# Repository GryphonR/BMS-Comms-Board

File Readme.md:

# eChook BMS Comunications Master Board
This project is heavily inspired by the [SimpBMS](https://github.com/Tom-evnut/SimpBMS) project by [Tom-evnut](https://github.com/Tom-evnut). The SimpBMS Hardware was never open-sourced, and has become obsolete post-COVID with the demise of the Teensy 3.x development boards.  
This board uses a Teensy 4.1 to mirror, then expand on the functionality of the original SimpBMS board.

While effort has been made to maintain some cross compatibility with the SimpBMS in connector choices and pinouts, this board is **not** a drop in replacement.

## License
This hardware design is released under a non-commercial open hardware licence, is provided **"as is"**, without warranty of any kind, express or implied. See the License.md file for details.

## Features

**ALL UNTESTED**

In addition to an expanded feature set over the SimpBMS, this board offers far more comprehensive circuit protection, most notably offering electrically isolated power and comms for the Battery Module connections, short circuit protection on all off board voltage feeds, so a harness issue does not take down the BMS, and 24v overvoltage protection on all digital and analogue inputs.

IO Overview:  
- 3 CAN Busses (All ESD protected, one Isolated for Battery Module comms).
    - Switchable Terminating Resistor for each bus.
- 2 UART, ESD protected and buffered.
    - One Isolated for Tesla Battery Module Comms.
    - One non-isolated, with selectable voltage levels.
- 1 RS-458/Modbus Interface
- 4 24v safe digital inputs
- 4 Monitored and Overcurrent protected 12v 5A High Side Drivers
- 4 5A Low Side Drivers
- 3 Short Circuit protected 12v outputs
- 4 Short Circuit Protected 5V outputs (One Isolated)
- 2 Analogue Inputs for Current Sensor signals, 24V safe.
- 1 I2C header for 0.91" OLED display.
- 1 SD card slot on the Teensy 4.1 to allow for logging with RTC timestamping.
- Ultra Bright Red error LED
- Warning Buzzer indicating BMS error or blown fuse (On, unless actively turned off by Teensy)

A little more detail:  
- Networks:
    - Electronically isolated communication busses for battery slave module communications.
        - Isolated 5V UART port for Tesla Module Communications (Teensy Serial2)
        - Isolated 600mA 5V supply 
        - Isolated CAN (Teensy CAN1) Connection for (most other) battery modules that communicate over CAN
    - Two non-isolated CAN busses, one exposed on the RJ-45 connector (CAN3), a second exposed on the J5 Auxillary Comms connector (CAN2)
    - One RS-485/MODBUS interface (Teensy Serial8)
    - RJ-45 connector with VICTRON compatible pin out as default, but 'Pick Your Own Pinout' pads on the bottom of the board to allow this to be modified to any application with a bit of soldering.
    - Serial output on J5 (Serial7). Voltage is selectable between 5V and 3.3v by solder jumper on rear of board.
- I/O
    - 4 High Impedence digital inputs, up to 24V.
    - 4 12V High Side Driver outputs, each with voltage, current and temperature monitoring, automatic over temperature, short circuit protection and error state reporting.
    - 4 PWM Capable Low Side Driver outputs with over current/short circuit protection, over temperature protecton. LOW Speed PWM only - testing needed, suspect <2KHz.
- Voltage Supply
    - 5V 500mA Isolated voltage supply for Tesla BMS Boards. Short circuit protected with red fault LED
    - 3 5V 500mA Voltage supplies on J2, J4 and J5, each short circuit protected with red fault LED
    - 3 12v Supplies on J4, Pins 10 and 11 sharing one short circuit protection ciruit, Pin 9 with it's own short circuit protection circuit.
- Warning System
    - Audible warning via a buzzer. This sounds if the onboard fuse blows, or if it is not actively being turned off by the Teensy.
    - Visual warning via 10mA Red LED. This is driven by the Teensy.
    - Heartbeat - Green LED located in cheesy silkscreen image of a heart will blink regularly if the system is healthy.

## Firmware
Due to the swap to a Teensy 4.1, expanded capabilities of the board, and a few pinout changes that go along with both of those, this board is not directly compatible with the SimpBMS code. There is an updated fork of the TeslaBMSV2 firmware adapted for this board here **TODO - link**.

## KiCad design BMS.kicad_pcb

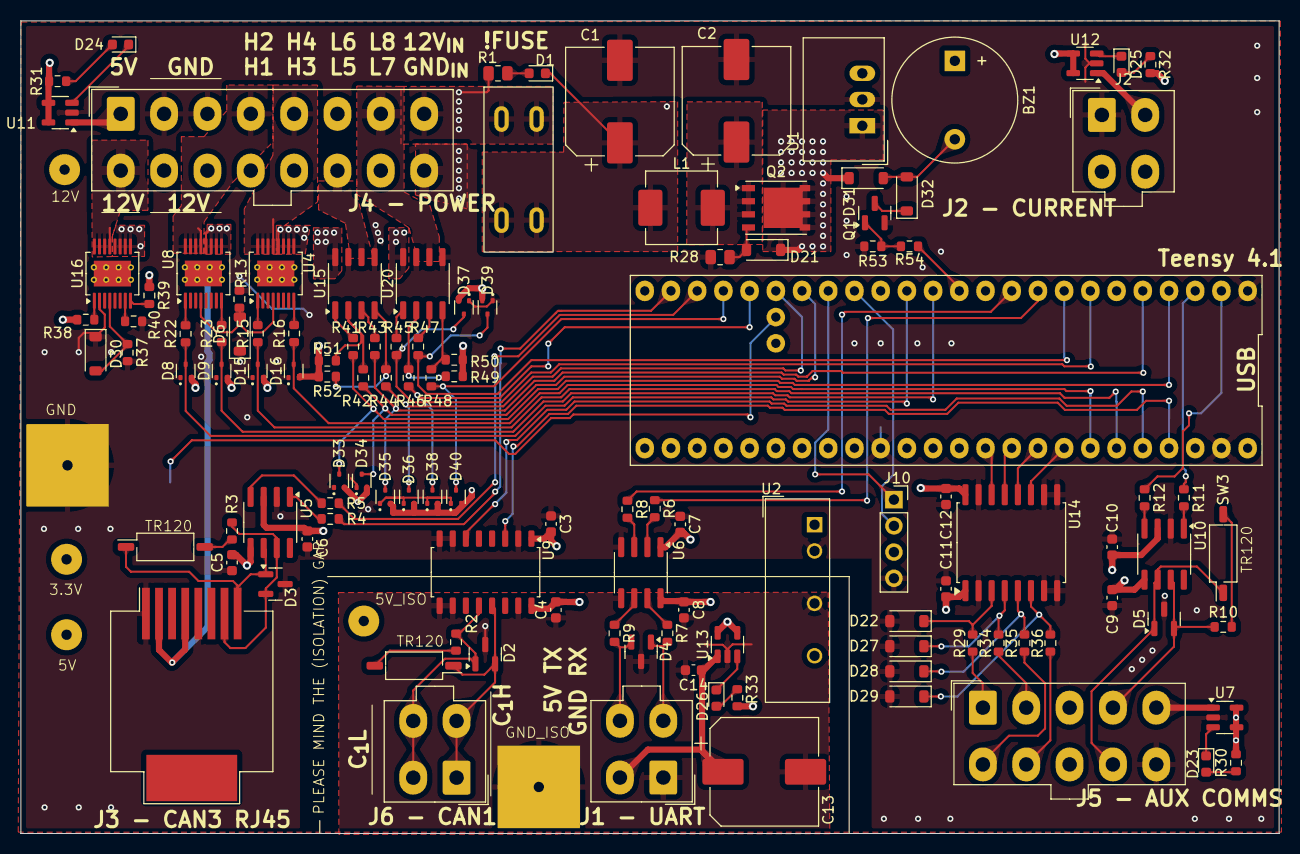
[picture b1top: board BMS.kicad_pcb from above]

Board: 4 copper layers, 121.9 x 78.7 mm, 127 parts (1 on the bottom side), 108 nets.

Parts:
BT1: Battery_Cell; BatteryHolder_Keystone_1060_1x2032
BZ1: Buzzer; Buzzer_12x9.5RM7.6
C1, C2, C13: 470uF; CP_Elec_10x10
C3, C4, C5, C6, C7, C8, C9, C10, C11, C12, C14: 1uF; C_0603_1608Metric
D1: LED; LED_0603_1608Metric
D2, D3, D4, D5: PESD1CAN; SOT-23
D6, D30, D31, D32: D; D_SOD-123
D8, D9, D15, D16, D33, D34, D35, D36, D37, D38, D39, D40: BAT54S; SOT-523
D21: 10V; D_SOD-123
D22, D27, D28, D29: 4.7V Zener 500mW; D_SOD-123
D23, D24, D25, D26: LED_RED; LED_0603_1608Metric
F1: Mini Blade Fuse (10A); XFCN XF-508P-B-B
J1, J2, J6: Conn_02x02_Counter_Clockwise; Molex_Mini-Fit_Jr_5566-04A_2x02_P4.20mm_Vertical
J3: RJ45; RJ45_Molex_0855135013_Vertical
J4: Conn_02x08_Top_Bottom; Molex_Mini-Fit_Jr_5566-16A_2x08_P4.20mm_Vertical
J5: Conn_02x05_Top_Bottom; Molex_Mini-Fit_Jr_5566-10A_2x05_P4.20mm_Vertical
J10: OLED; PinSocket_1x04_P2.54mm_Vertical
L1: 1.5uH; L_Changjiang_FXL0618
Q1: BSS138LT1G; SOT-23
Q2: HSBA100P03; PowerPAK_SO-8_Single
R1, R28: 10k; R_0805_2012Metric
R2, R3, R10: 120; R_0603_1608Metric
R4, R5, R6, R7, R8, R9, R11, R12: 330R; R_0603_1608Metric
R13, R29, R34, R35, R36, R37, R53: 4.7k; R_0603_1608Metric
R15, R16, R22, R23, R38, R39: 15k; R_0603_1608Metric
R30, R31, R32, R33: 3.3k; R_0603_1608Metric
R40, R41, R42, R43, R44, R45, R46, R47, R48: 1k; R_0603_1608Metric
R49, R50, R51, R52: 47k; R_0603_1608Metric
R54: 330; R_0603_1608Metric
SW1, SW2, SW3: SW_DIP_x01; SW_DIP_SPSTx01_Slide_Copal_CHS-01B_W7.62mm_P1.27mm
TP1, TP4: TestPoint; Clip_TP
TP2, TP3, TP5, TP6: TestPoint; STD_TP
U1: K7805M-1000R3; Converter_DCDC_TRACO_TSR-1_THT
U2: B0505S-3WR2; Converter_DCDC_TRACO_TBA1-xxxxE_Single_THT
U3: Teensy4.1; Teensy_4.1_RTC
U4, U8, U16: VND7050AJTR; PowerSSO-16-1EP_3.9x4.9mm_P0.5mm_EP2.5x3.61mm_ThermalVias
U5, U10: TJA1051T/3/1J; SOIC-8_3.9x4.9mm_P1.27mm
U6: ISO7331C; SOIC-8_3.9x4.9mm_P1.27mm
U7, U11, U12, U13: TPS2051CDBV; SOT-23-5
U9: ISO1050DWR; SOP-16_4.55x10.3mm_P1.27mm
U14: CA-IS3740; SOIC-16W_7.5x10.3mm_P1.27mm
U15, U20: VNLD5090TR-E; SO-8_3.9x4.9mm_P1.27mm

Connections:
+3.3V: C3.2, C5.2, C7.2, C9.2, C12.2, D8.2 (K), D9.2 (K), D15.2 (K), D16.2 (K), D33.2 (K), D34.2 (K), D35.2 (K), D36.2 (K), D37.2 (K), D38.2 (K), D39.2 (K), D40.2 (K), J10.3, R49.2, R50.2, R51.2, R52.2, TP6.1, U3.15 (3V3), U3.46 (3V3), U3.50 (3.3V), U5.5 (Vref), U6.1 (VCC1), U9.1 (VCC1), U10.5 (Vref), U14.16 (VDD_{B})
+5V: C6.2, C10.2, C11.1, R30.2, R31.2, R32.2, R38.1, R39.1, TP5.1, U1.3 (Vout), U2.1 (+Vin), U3.48 (VIN), U5.3 (VDD), U7.4 (EN), U7.5 (IN), U10.3 (VDD), U11.4 (EN), U11.5 (IN), U12.4 (EN), U12.5 (IN), U14.1 (VDD_{A})
+5V_ISO: C4.2, C8.2, R33.2, TP3.1, U2.6 (+Vout), U6.8 (VCC2), U9.16 (VCC2), U13.4 (EN), U13.5 (IN)
+12V: D21.1 (K), D31.1 (K), J3.2, J3.4, Q2.5 (D), TP2.1, U1.1 (Vin), U4.17 (V_{cc}), U8.17 (V_{cc}), U16.17 (V_{cc})
/12V_INPUT: BZ1.1 (+), F1.1, J4.8, R1.2
/12V_Out_Bank1: J4.9, U16.13 (Output_0), U16.14 (Output_0), U16.15 (Output_0), U16.16 (Output_0)
/12V_Out_Bank2: J4.10, J4.11, U16.9 (Output_1), U16.10 (Output_1), U16.11 (Output_1), U16.12 (Output_1)
/12V_Output_Protection/Driver_Gnd: D30.2 (A), R37.1, U16.4 (GND)
/Buzzer_-ve: D32.1 (K), Q1.3 (D)
/Buzzer_Logic: R54.2, U3.12 (10_CS_MQSR)
/CAN1_HIGH_ISO: D2.2 (A2), J6.1, J6.3, SW1.1, U9.13 (CANH)
/CAN1_LOW_ISO: D2.1 (A1), J6.2, J6.4, R2.1, U9.12 (CANL)
/CAN1_RX: U3.45 (23_A9_CRX1_MCLK1), U9.3 (RXD)
/CAN1_TX: U3.44 (22_A8_CTX1), U9.6 (TXD)
/CAN2_HIGH: D5.2 (A2), J5.4, R10.1, U10.7 (CANH)
/CAN2_LOW: D5.1 (A1), J5.9, SW3.1, U10.6 (CANL)
/CAN2_RX: R12.1, U3.2 (0_RX1_CRX2_CS1)
/CAN2_TX: R11.1, U3.3 (1_TX1_CTX2_MISO1)
/CAN3_HIGH: D3.2 (A2), J3.7, R3.1, U5.7 (CANH)
/CAN3_LOW: D3.1 (A1), J3.8, SW2.1, U5.6 (CANL)
/CAN3_RX: R5.1, U3.22 (30_CRX3)
/CAN3_TX: R4.1, U3.23 (31_CTX3)
/High Side Drivers/Driver_Gnd: D6.2 (A), R13.1, U4.4 (GND), U8.4 (GND)
/In_1: J5.1, R29.1
/In_2: J5.2, R34.1
/In_3: J5.6, R35.1
/In_4: J5.7, R36.1
/Logic_IN_1: U3.38 (16_A2_RX4_SCL1), U14.14 (Out_{1})
/Logic_IN_2: U3.39 (17_A3_TX4_SDA1), U14.13 (Out_{2})
/Logic_IN_3: U3.40 (18_A4_SDA), U14.12 (Out_{3})
/Logic_IN_4: U3.41 (19_A5_SCL), U14.11 (Out_{4})
/OUT1_HSD_LOGIC: D9.3 (COM), R23.1, U3.13 (11_MOSI_CTX1)
/OUT1_HSD_PWR: J4.12, U8.9 (Output_1), U8.10 (Output_1), U8.11 (Output_1), U8.12 (Output_1)
/OUT2_HSD_LOGIC: D8.3 (COM), R22.1, U3.14 (12_MISO_MQSL)
/OUT2_HSD_PWR: J4.4, U8.13 (Output_0), U8.14 (Output_0), U8.15 (Output_0), U8.16 (Output_0)
/OUT3_HSD_LOGIC: D16.3 (COM), R16.1, U3.42 (20_A6_TX5_LRCLK1)
/OUT3_HSD_PWR: J4.13, U4.9 (Output_1), U4.10 (Output_1), U4.11 (Output_1), U4.12 (Output_1)
/OUT4_HSD_LOGIC: D15.3 (COM), R15.1, U3.43 (21_A7_RX5_BCLK1)
/OUT4_HSD_PWR: J4.5, U4.13 (Output_0), U4.14 (Output_0), U4.15 (Output_0), U4.16 (Output_0)
/OUT5_LSD_LOGIC: D33.3 (COM), R41.1, U3.4 (2_OUT2)
/OUT5_LSD_PWR: J4.14, U15.6 (Drain_{2})
/OUT5_LSD_Status: D34.3 (COM), R42.1, U3.18 (26_A12_MOSI1)
/OUT6_LSD_LOGIC: D35.3 (COM), R43.1, U3.5 (3_LRCLK2)
/OUT6_LSD_PWR: J4.6, U15.8 (Drain_{1})
/OUT6_LSD_Status: D36.3 (COM), R44.1, U3.19 (27_A13_SCK1)
/OUT7_LSD_LOGIC: D37.3 (COM), R45.1, U3.7 (5_IN2)
/OUT7_LSD_PWR: J4.7, U20.6 (Drain_{2})
/OUT7_LSD_Status: D38.3 (COM), R46.1, U3.20 (28_RX7)
/OUT8_LSD_LOGIC: D39.3 (COM), R47.1, U3.8 (6_OUT1D)
/OUT8_LSD_PWR: J4.15, U20.8 (Drain_{1})
/OUT8_LSD_Status: D40.3 (COM), R48.1, U3.21 (29_TX7)
/Overcurrent_Protection1/V_{OUT}: J4.1, U11.1 (OUT)
/Overcurrent_Protection2/V_{OUT}: J2.2, U12.1 (OUT)
/Overcurrent_Protection3/V_{OUT}: C13.1, C14.1, J1.2, U13.1 (OUT)
/Overcurrent_Protection/V_{OUT}: J5.5, U7.1 (OUT)
/RTC_BATT_+: BT1.1 (+), U3.49 (V_BATT_RTC)
/SERIAL_RX: R6.1, U3.9 (7_RX2_OUT1A)
/SERIAL_TX: R8.1, U3.10 (8_TX2_IN1)
/UART_RX_ISO: D4.1 (A1), J1.3, R7.2
/UART_TX_ISO: D4.2 (A2), J1.4, R9.2
GND: BT1.2 (-), C1.2, C2.2, C3.1, C5.1, C6.1, C7.1, C9.1, C10.1, C11.2, C12.1, D3.3 (common), D5.3 (common), D6.1 (K), D8.1 (A), D9.1 (A), D15.1 (A), D16.1 (A), D22.2 (A), D27.2 (A), D28.2 (A), D29.2 (A), D30.1 (K), D33.1 (A), D34.1 (A), D35.1 (A), D36.1 (A), D37.1 (A), D38.1 (A), D39.1 (A), D40.1 (A), J2.1, J3.1, J3.5, J4.2, J4.3, J4.16, J5.10, J10.4, Q1.2 (S), R13.2, R28.1, R37.2, R40.1, R53.2, TP4.1, U1.2 (GND), U2.2 (-Vin), U3.1 (GND), U3.34 (GND), U3.47 (GND), U5.2 (VSS), U6.4 (GND1), U7.2 (GND), U9.2 (GND1), U9.7 (GND1), U9.8 (GND1), U10.2 (VSS), U11.2 (GND), U12.2 (GND), U14.2 (GND_{A}), U14.7 (EN_{A}), U14.8 (GND_{A}), U14.9 (GND_{B}), U14.10 (EN_{B}), U14.15 (GND_{B}), U15.5 (Source_{2}), U15.7 (Source_{1}), U16.2 (~FaultRST), U20.5 (Source_{2}), U20.7 (Source_{1})
GND_ISO: C4.1, C8.1, C13.2, C14.2, D2.3 (common), D4.3 (common), J1.1, TP1.1, U2.4 (-Vout), U6.5 (GND2), U9.9 (GND2), U9.10 (GND2), U9.15 (GND2), U13.2 (GND)
I2C_SCL: J10.2, U3.16 (24_A10_TX6_SCL2)
I2C_SDA: J10.1, U3.17 (25_A11_RX6_SDA2)
unnamed: BZ1.2 (-), D31.2 (A), D32.2 (A)
unnamed: C2.1, L1.2, Q2.1 (S), Q2.2 (S), Q2.3 (S)
unnamed: D1.2 (A), R1.1
unnamed: C1.1, D1.1 (K), F1.2, L1.1
unnamed: D21.2 (A), Q2.4 (G), R28.2
unnamed: D22.1 (K), R29.2, U14.3 (In_{1})
unnamed: D23.2 (A), R30.1
unnamed: D23.1 (K), U7.3 (~FLT)
unnamed: D24.2 (A), R31.1
unnamed: D24.1 (K), U11.3 (~FLT)
unnamed: D25.2 (A), R32.1
unnamed: D25.1 (K), U12.3 (~FLT)
unnamed: D26.2 (A), R33.1
unnamed: D26.1 (K), U13.3 (~FLT)
unnamed: D27.1 (K), R34.2, U14.4 (In_{2})
unnamed: D28.1 (K), R35.2, U14.5 (In_{3})
unnamed: D29.1 (K), R36.2, U14.6 (In_{4})
unnamed: Q1.1 (G), R53.1, R54.1
unnamed: R2.2, SW1.2
unnamed: R3.2, SW2.2
unnamed: R10.2, SW3.2
unnamed: R15.2, U4.1 (Input_0)
unnamed: R16.2, U4.8 (Input_1)
unnamed: R5.2, U5.4 (RXD)
unnamed: R4.2, U5.1 (TXD)
unnamed: R7.1, U6.7 (INA)
unnamed: R8.2, U6.3 (INB)
unnamed: R6.2, U6.2 (OUTA)
unnamed: R9.1, U6.6 (OUTB)
unnamed: R22.2, U8.1 (Input_0)
unnamed: R23.2, U8.8 (Input_1)
unnamed: R12.2, U10.4 (RXD)
unnamed: R11.2, U10.1 (TXD)
unnamed: R41.2, U15.1 (IN_{1})
unnamed: R43.2, U15.3 (IN_{2})
unnamed: R42.2, R51.1, U15.2 (Status_{1})
unnamed: R44.2, R52.1, U15.4 (Status_{2})
unnamed: R38.2, U16.1 (Input_0)
unnamed: R39.2, U16.8 (Input_1)
unnamed: R40.2, U16.7 (Multisense)
unnamed: R45.2, U20.1 (IN_{1})
unnamed: R47.2, U20.3 (IN_{2})
unnamed: R46.2, R49.1, U20.2 (Status_{1})
unnamed: R48.2, R50.1, U20.4 (Status_{2})

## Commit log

2025-04-19 Added isolated CAN, UART and PWR
2025-05-06 Adding BOM Info
2025-05-06 Adding Part Numbers
2025-05-06 Updated Isolated CANTX
2025-05-07 Connectors, high side circuits added, layout progressed
2025-05-08 Added LSD, HSD, Improved Layout
2025-05-12 Added 12v Out Protection, generally completed layout
2025-05-13 All the diodes, and other layout work
2025-05-15 Layout, smaller resistors and HB + Error LEDs
2025-05-15 Schematic Layout Improvements, Start of RS485 Circuit
2025-05-21 Finalised RS485 Circuit, Layout improvemnts, mounting holes, silkscreen...
2025-05-22 Added first draft Readme
2025-05-22 Pinout swapped for PWMable Error LED
2025-05-22 Readme update
2025-05-29 Added UART Buffer for Aux Connector Serial
2025-06-04 Added hieracical schematic for better 5V_OUT protection
2025-06-11 Fixed network pinouts - no shared pins now
2025-06-12 'Fixed' Molex Footprints - 2x8 not genuine molex, 4.2 instead of 5.5 RS
2025-06-16 ISOCAN footprint update, zone optimisations
2025-06-16 Schematic Net Colours
2025-06-16 PCB Improvements - VIAS/Pours UNFINISHED
2025-06-18 J5 Bottom Silkscreen, Schematic organise
2025-06-24 Further Schematic Tidy
2025-07-01 Implemented schematic review suggestions (Notes.txt)
2025-07-14 Corrected Can Transceiver Datasheet Link. Updated Kicad to 9.0.3
2025-07-14 Added 5V protection capacitors, altered 5V_ISO Output Caps, Corrected RX<>TX for Serial3
2025-07-15 Added pulldown safety resistors, layout improvements
2025-07-24 Post Chris Layout Review
2025-08-06 Updated RPP Mosfet to 100V device
2025-08-06 Placed RPP in front of Pi Filter, to protect electrolytics from RP
2025-08-06 added 12v Feed Error LEDs
2025-08-06 Error LED defaults to ON, driven OFF by Teensy
2025-08-06 Rear Silkscreen labels and Buzzer solder jumper
2025-08-06 Added Silkscreen Labels
2025-08-07 Pinout Review Complete, Altenative option for ISO CAN IC added
2025-08-07 V0.1 as Manufactured
